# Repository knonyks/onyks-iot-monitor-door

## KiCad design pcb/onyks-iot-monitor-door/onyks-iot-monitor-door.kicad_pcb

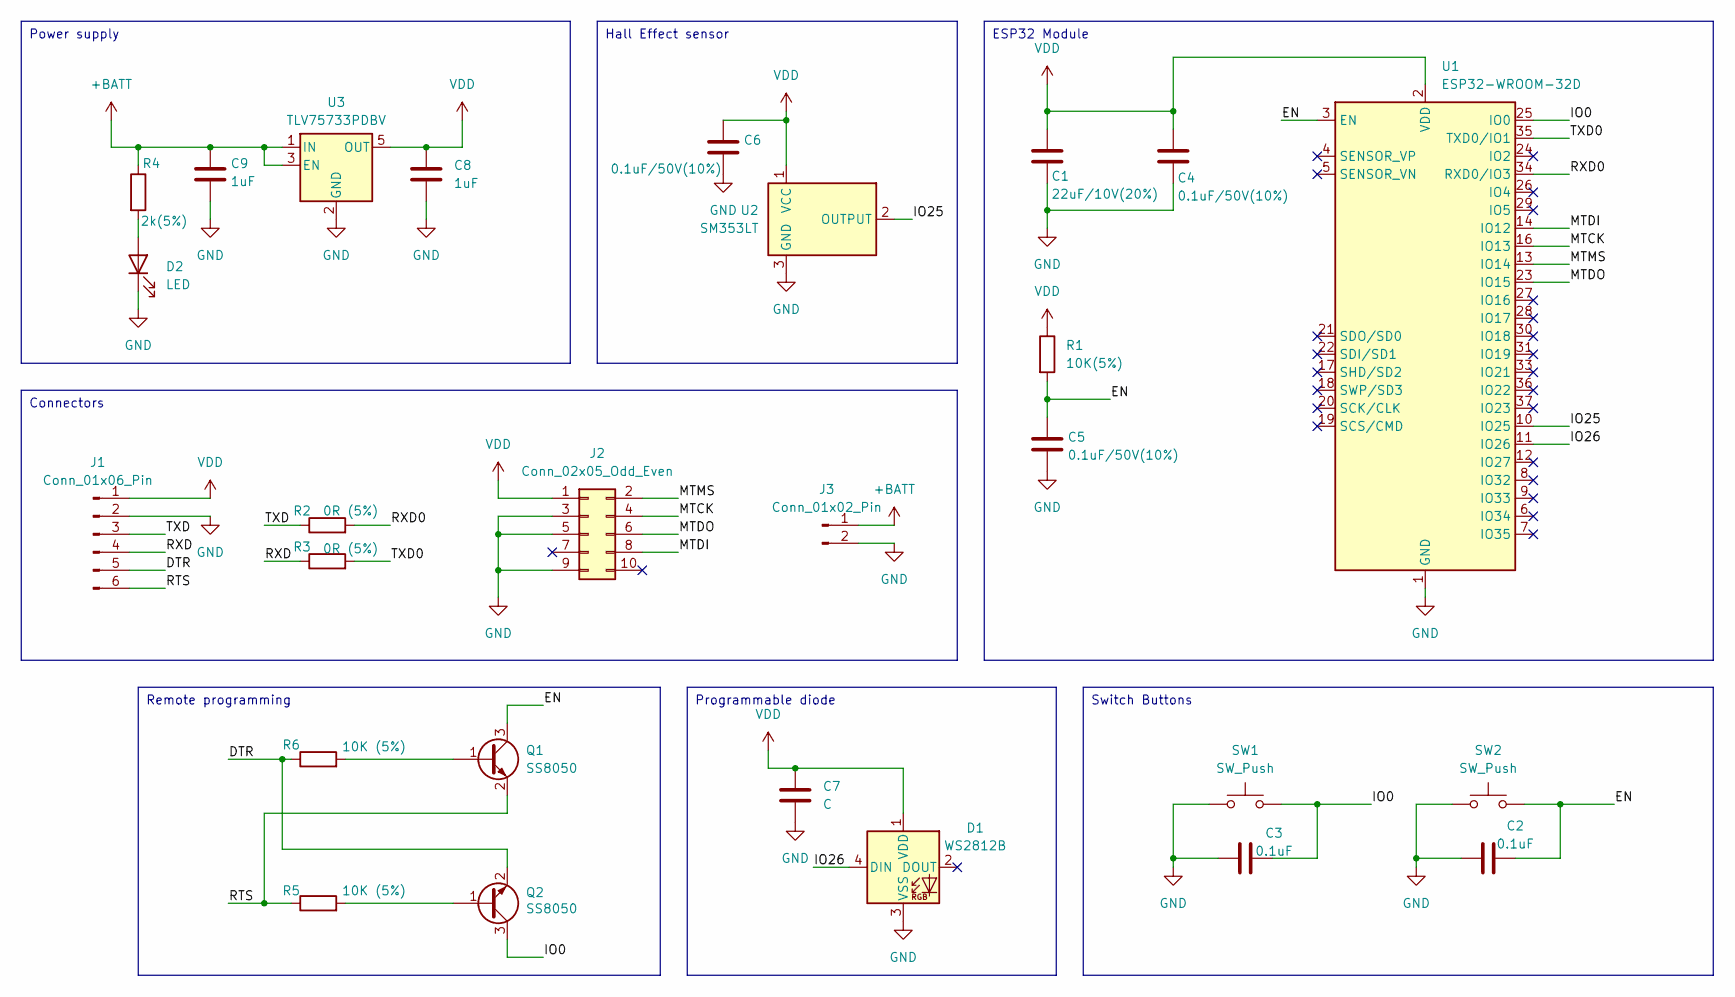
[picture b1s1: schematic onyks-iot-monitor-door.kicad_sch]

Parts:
C1: 22uF/10V(20%); C_0603_1608Metric
C2, C3: 0.1uF; C_0603_1608Metric
C4, C5, C6: 0.1uF/50V(10%); C_0603_1608Metric
C7: C; C_0603_1608Metric
C8, C9: 1uF; C_0603_1608Metric
D1: WS2812B; LED_WS2812B_PLCC4_5.0x5.0mm_P3.2mm
D2: LED; LED_0201_0603Metric
J1: Conn_01x06_Pin; PinHeader_1x06_P2.54mm_Vertical
J2: Conn_02x05_Odd_Even; PinHeader_2x05_P2.54mm_Vertical
J3: Conn_01x02_Pin; PinHeader_1x02_P2.54mm_Vertical
Q1, Q2: SS8050; SOT-23
R1: 10K(5%); R_0603_1608Metric
R2, R3: 0R (5%); R_0603_1608Metric
R4: 2k(5%); R_0603_1608Metric
R5, R6: 10K (5%); R_0603_1608Metric
SW1, SW2: SW_Push; SW_Tactile_SPST_NO_Straight_CK_PTS636Sx25SMTRLFS
U1: ESP32-WROOM-32D
U2: SM353LT; SOT-23
U3: TLV75733PDBV; SOT-23-5

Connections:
+BATT: C9.1, J3.1, R4.1, U3.1 (IN), U3.3 (EN)
/DTR: J1.5, Q2.2 (E), R6.1
/EN: C2.2, C5.1, Q1.3 (C), R1.2, SW2.2, U1.3 (EN)
/IO0: C3.2, Q2.3 (C), SW1.2, U1.25 (IO0)
/IO25: U1.10 (IO25), U2.2 (OUTPUT)
/IO26: D1.4 (DIN), U1.11 (IO26)
/MTCK: J2.4, U1.16 (IO13)
/MTDI: J2.8, U1.14 (IO12)
/MTDO: J2.6, U1.23 (IO15)
/MTMS: J2.2, U1.13 (IO14)
/RTS: J1.6, Q1.2 (E), R5.1
/RXD: J1.4, R3.1
/RXD0: R2.2, U1.34 (RXD0/IO3)
/TXD: J1.3, R2.1
/TXD0: R3.2, U1.35 (TXD0/IO1)
GND: C1.2, C2.1, C3.1, C4.2, C5.2, C6.2, C7.2, C8.2, C9.2, D1.3 (VSS), D2.1 (K), J1.2, J2.3, J2.5, J2.9, J3.2, SW1.1, SW2.1, U1.1 (GND), U1.15 (GND), U1.38 (GND), U1.39 (GND), U2.3 (GND), U3.2 (GND)
unnamed: D2.2 (A), R4.2
unnamed: Q1.1 (B), R6.2
unnamed: Q2.1 (B), R5.2
VDD: C1.1, C4.1, C6.1, C7.1, C8.1, D1.1 (VDD), J1.1, J2.1, R1.1, U1.2 (VDD), U2.1 (VCC), U3.5 (OUT)

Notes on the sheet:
ESP32 Module
Connectors
Programmable diode
Remote programming
Switch Buttons
Hall Effect sensor
Power supply

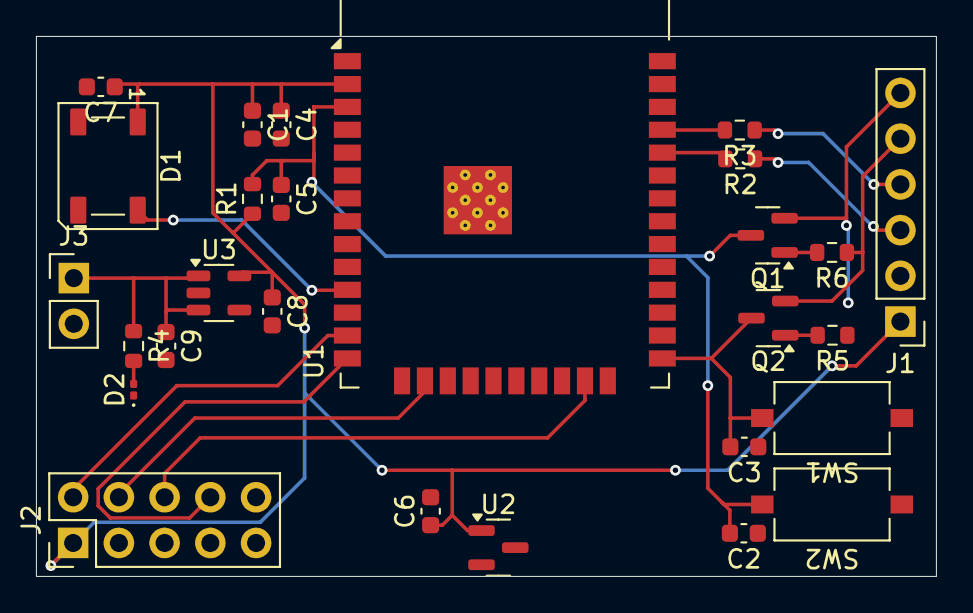
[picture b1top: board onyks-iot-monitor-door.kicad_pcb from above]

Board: 2 copper layers, 50.0 x 30.0 mm, 27 parts (0 on the bottom side), 20 nets.

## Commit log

2024-11-18 Initial template with README
2024-11-25 Add basic components to the schematic
2024-12-11 Finish schemat and pcb design (no GND)
